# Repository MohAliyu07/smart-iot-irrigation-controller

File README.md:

# Smart IoT Irrigation Controller v2

A four-zone garden watering controller built around the ESP32-S3. It reads four soil-moisture sensors and a DHT11, decides which zones need water, and runs a 12 V pump through four solenoid valves. You can watch it and take over from your phone through Blynk.

This repo has everything for v2: firmware, the PCB, simulations, test results and the technical report.

The current board is **Rev B**, a 100 × 75 mm rectangular board redrawn from the schematic up. The first board (Rev A, the round one) is still here for reference.

## What it does

- Waters each zone on its own. A zone starts below 35 % moisture and stops above 60 % (both adjustable from Blynk).
- Opens at most two valves at once, so the 12 V 3 A adapter is never overloaded.
- Soft-starts the pump over 500 ms with 20 kHz PWM, which cut the start-up peak from 2.98 A to 1.62 A in the performance model.
- Checks the current on every step of the soft start, so a stalled pump is stopped during the ramp (2.54 A after 429 ms in the model).
- Measures pump current with a 20 mΩ shunt and an INA181, and stops the pump within 250 ms on:
  - overcurrent above 2.5 A (jammed pump),
  - dry run below 0.25 A (empty tank),
  - supply voltage outside 10.5–13.8 V.
- Caps every watering run at 20 minutes in case a sensor fails.
- Skips a zone whose soil sensor is shorted, open or unplugged.
- Has three modes (auto, manual and off), a MODE button, a buzzer for faults and a Wi-Fi status LED.

## Hardware

- **MCU:** ESP32-S3-WROOM-1-N8
- **Inputs:** 4 capacitive soil-moisture sensors (power switched by a P-FET to cut corrosion and current), DHT11, supply sense divider (100k/22k), pump current sense
- **Outputs:** 12 V DC pump (PWM low-side MOSFET), 4 × 12 V solenoid valves, buzzer, LEDs
- **Board (Rev B):** 100 × 75 mm rectangle with four M3 mounting holes, routed in EasyEDA Pro with 0 DRC errors and 100 % of nets routed. The DC jack and USB-C face out of the left edge, the pump and valve terminals are along the bottom edge, and the sensor connectors are on the right. The antenna sits at the top edge over a copper keep-out.

### What changed from Rev A to Rev B

- Pump MOSFET changed from AO3400A (SOT-23) to AO4404B (SOIC-8) for more current and heat margin.
- A 1 kΩ + 100 nF filter was added on the current-sense output, because the shunt only carries current during the PWM on-time.
- High-current tracks are 1.4–1.5 mm wide with no vias. Power parts are grouped on the left, away from the antenna and the sensor inputs.
- Unused pins are marked no-connect, and the board has mounting holes.
- Pin assignments are the same, so the pin map in `config.h` did not change.

The schematic is in [hardware/rev-b/schematic/RevB_Schematic.pdf](hardware/rev-b/schematic/RevB_Schematic.pdf). All 7 sheets:

**Sheet 1: Power input**

**Sheet 2: Regulators and USB**

**Sheet 3: ESP32-S3**

**Sheet 4: Soil sensors and DHT11**

**Sheet 5: Pump driver and buzzer**

**Sheet 6: Valves 1 and 2**

**Sheet 7: Valves 3 and 4**

The routed board, with the top copper in red, the bottom copper in blue and the ground pours on both layers:

## Repository layout

| Folder | What's inside |
|---|---|
| `firmware/` | PlatformIO project (Arduino on ESP32-S3) |
| `hardware/rev-b/fab/` | Rev B Gerbers, BOM and pick-and-place from EasyEDA Pro |
| `hardware/rev-b/schematic/` | Rev B schematic, PDF and one PNG per sheet |
| `hardware/rev-a-fab/` | Rev A (round board) Gerbers, BOM and pick-and-place |
| `hardware/kicad/` | Rev A KiCad 10 project |
| `hardware/altium/` | Rev A Altium schematic and PCB |
| `hardware/3d/` | Rev A STEP model |
| `simulation/wokwi/` | Wokwi ESP32-S3 simulation (sketch, diagram, libraries) |
| `simulation/proteus/` | Proteus project, test hex and the automated test runner |
| `simulation/avr-emulator/` | Python AVR emulator used to run the Proteus test firmware and measure timing |
| `simulation/performance-model/` | Plant model in C++ that is compiled with the real firmware sources, plus the CSV output |
| `results/` | Test results workbook and performance graphs |
| `docs/` | Technical report for Rev A (PDF) and the Rev B change notes |
| `images/` | Board and circuit pictures |

## Building the firmware

1. Install [PlatformIO](https://platformio.org/).
2. Copy `firmware/include/secrets.example.h` to `firmware/include/secrets.h` and put in your Wi-Fi name, password and Blynk token. `secrets.h` is git-ignored, so it won't be committed.
3. From `firmware/`, run `pio run -t upload`.

Pin assignments and every limit live in `firmware/include/config.h`.

### Blynk virtual pins

| Pin | Use |
|---|---|
| V0–V3 | Moisture % for zones 1–4 |
| V4, V5 | Temperature, humidity |
| V6 | Supply voltage |
| V7 | Pump current |
| V8 | Mode (0 auto, 1 manual, 2 off) |
| V9 | Fault code |
| V10–V13 | Manual valve switches |
| V14, V15 | Dry and wet thresholds |
| V16 | Clear fault |

## Simulation and testing

- **Wokwi:** open a new ESP32-S3 project and paste in the three files from `simulation/wokwi/`. The pots stand in for the sensors. See that folder's README for the pin map.
- **Proteus:** `simulation/proteus/Irrigation_v2_Sim.pdsprj` runs a stepped test of the pump, valve and alarm outputs.
- **Performance model:** Wokwi only runs at about 3 % of real time, so long runs (an 8-hour watering day, a jammed pump, a dry tank) were done in the C++ model.

```bash
cd simulation/performance-model
F=../../firmware
g++ -O2 -std=c++17 -DREVA -o simA sim.cpp && ./simA
g++ -O2 -std=c++17 -Istub -I$F/include -o sim sim.cpp $F/src/sensors.cpp $F/src/outputs.cpp $F/src/zones.cpp && ./sim
python3 plot.py
```

| Result | Value |
|---|---|
| Most valves open at once | 2 (limit 2) |
| Peak running current | 1.59 A (limit 2.5 A) |
| Soft-start peak | 1.62 A (2.98 A hard start) |
| Dry-run and overcurrent trip time | 250 ms |
| Low-supply trip time | 200–250 ms, tested at 8 points of the 10 s sensor period |
| Faults in a normal 8-hour run | 0 |
| Current-sense error during soft start | 0.01 A mean on Rev B (0.34 A on Rev A) |
| Stalled pump at start-up | stopped at 2.54 A after 429 ms on Rev B (2.94 A, 499 ms on Rev A) |

These numbers come from the model. The Rev B sketch compiles and runs in Wokwi (steady readings, no fault), but the fault tests were not repeated there. The firmware has not been built with PlatformIO or run on a board yet, and Proteus was last run on the Rev A code.

### Proteus check (early logic test)

Before the ESP32 firmware was ready, I tested the watering logic in Proteus on a simplified ATmega328P version. This was done on the Rev A code, not on the Rev B board. Four potentiometers stand in for the soil sensors, a DHT11 gives temperature and humidity, a push button and a switch act as the manual and tank-level inputs, and six LEDs show the pump, the four valves and the alarm. All 6 Proteus tests passed. The project is in `simulation/proteus/`.

The full write-up, including Rev B, is in [docs/Technical_Report_RevB.pdf](docs/Technical_Report_RevB.pdf). The Rev B changes are also listed in [docs/CHANGES_RevB.md](docs/CHANGES_RevB.md).

## Author

Mohammed Olamilekan Aliyu, Electronics Engineer

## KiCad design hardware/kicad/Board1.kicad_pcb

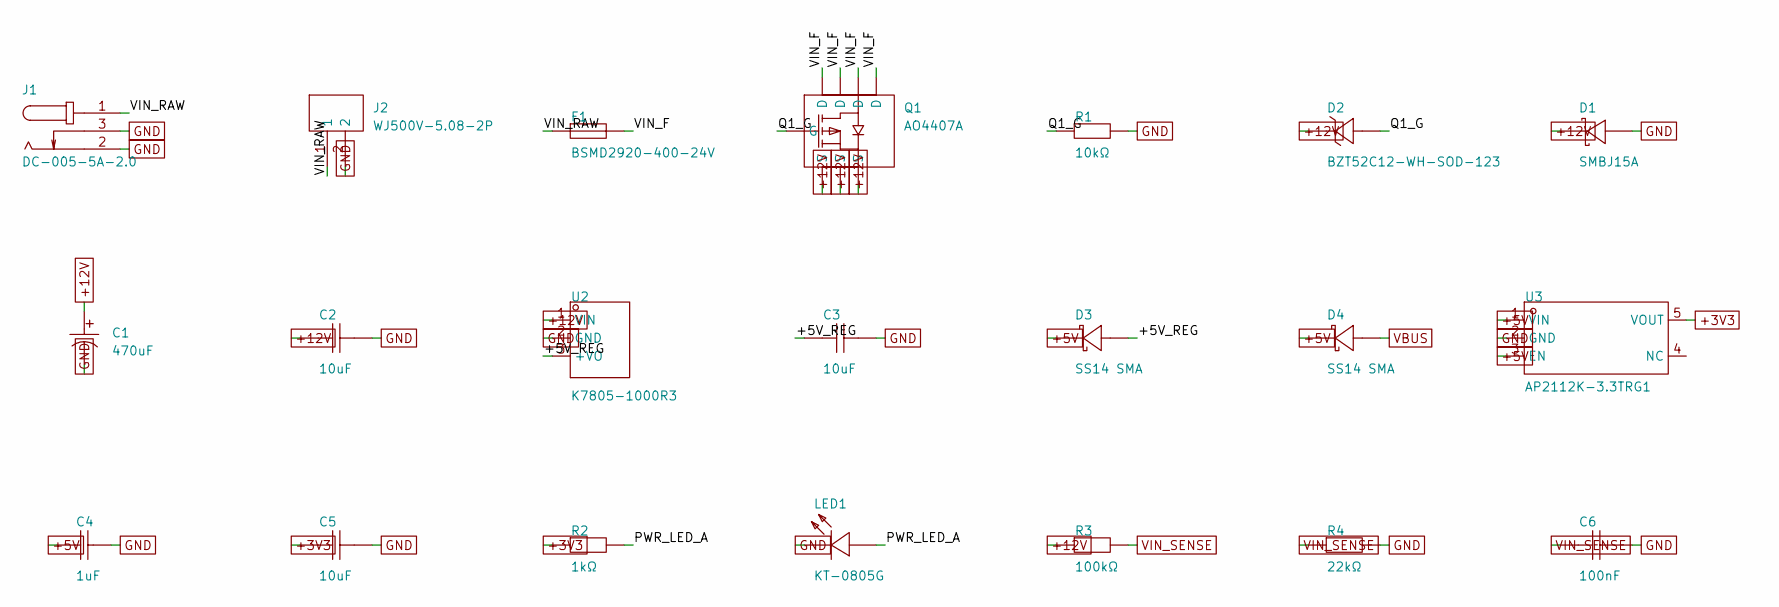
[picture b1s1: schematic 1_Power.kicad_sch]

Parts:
C1: 470uF; CAP-SMD_BD10.0-L10.3-W10.3-LS11.0-FD; TOLERANCE ±20%; VOLTAGE RATING 25V; MANUFACTURER PART RVT1E471M1010; JLCPCB PART CLASS Extended Part
C2, C3, C5: 10uF; C0805; TOLERANCE ±10%; VOLTAGE RATING 25V; MANUFACTURER PART CL21A106KAYNNNE; LCSC PART NAME 10uF ±10% 25V
C4: 1uF; C0805; TOLERANCE ±10%; VOLTAGE RATING 50V; MANUFACTURER PART CL21B105KBFNNNE; JLCPCB PART CLASS Basic Part
C6: 100nF; C0805; TOLERANCE ±10%; VOLTAGE RATING 50V; MANUFACTURER PART CC0805KRX7R9BB104; LCSC PART NAME 100nF ±10% 50V
D1: SMBJ15A; SMB_L4.6-W3.6-LS5.3-RD; BREAKDOWN VOLTAGE 16.7V; MANUFACTURER PART SMBJ15A; LCSC PART NAME SMBJ15A
D2: BZT52C12-WH-SOD-123; SOD-123_L2.7-W1.7-LS3.8-RD; ZENER VOLTAGE(NOM) 12V; ZENER VOLTAGE(RANGE) 11.4V~12.7V; MANUFACTURER PART BZT52C12-WH-SOD-123; LCSC PART NAME 独立式 耐压:12V 电流:0.1uA@9V
D3, D4: SS14 SMA; SMA_L4.3-W2.6-LS5.1-RD; VOLTAGE - FORWARD(VF@IF) 550mV@1A; VOLTAGE - DC REVERSE(VR) 40V; MANUFACTURER PART SS14 SMA; LCSC PART NAME 电压:40V 电流:1A
F1: BSMD2920-400-24V; F2920; VOLTAGE - MAX 24V; MANUFACTURER PART BSMD2920-400-24V; JLCPCB PART CLASS Extended Part
J1: DC-005-5A-2.0; DC-IN-TH_DC-005-5A-2.0; CURRENT RATING 5A; VOLTAGE RATING (MAX) 24V; MANUFACTURER PART DC-005-5A-2.0; LCSC PART NAME DC电源插座 内径:2mm 外径:6.2mm
J2: WJ500V-5.08-2P; CONN-TH_2P-P5.00_WJ500V-5.08-2P; CURRENT RATING 18A; VOLTAGE RATING (MAX) 250V; MANUFACTURER PART WJ500V-5.08-2P; LCSC PART NAME 1x2P 5.08mm 直插 排数:1 每排P数:2
LED1: KT-0805G; LED0805-R-RD; VOLTAGE - FORWARD(VF) 2.6V~3.1V; MANUFACTURER PART KT-0805G; LCSC PART NAME 0805 翠绿 高亮
Q1: AO4407A; SOIC-8_L4.9-W3.9-P1.27-LS6.0-BL; MANUFACTURER PART AO4407A; LCSC PART NAME 1个P沟道 耐压:30V 电流:12A
R1: 10kΩ; R0805; TOLERANCE ±1%; VOLTAGE-SUPPLY(MAX) 150V; MANUFACTURER PART 0805W8F1002T5E; LCSC PART NAME 厚膜电阻 10kΩ ±1%
R2: 1kΩ; R0805; TOLERANCE ±1%; MANUFACTURER PART 0805W8F1001T5E; LCSC PART NAME 1kΩ ±1% 125mW 厚膜电阻
R3: 100kΩ; R0805; TOLERANCE ±1%; MANUFACTURER PART 0805W8F1003T5E (SMT业务专用); LCSC PART NAME 100kΩ ±1%
R4: 22kΩ; R0805; TOLERANCE ±1%; VOLTAGE-SUPPLY(MAX) 150V; MANUFACTURER PART 0805W8F2202T5E; LCSC PART NAME 厚膜电阻 22kΩ ±1%
U2: K7805-1000R3; PWRM-TH_K78XX-2000; VOLTAGE - SUPPLY 8V~36V; OUTPUT VOLTAGE -5V；5V; MANUFACTURER PART K7805-1000R3; LCSC PART NAME DC/DC模块电源，宽电压输入，非隔离稳压单路输出
U3: AP2112K-3.3TRG1; SOT-25-5_L2.9-W1.6-P0.95-LS2.8-BL; VOLTAGE - SUPPLY 6V; OUTPUT VOLTAGE 3.3V; MANUFACTURER PART AP2112K-3.3TRG1; LCSC PART NAME 3.3V 600mA 6V

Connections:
+3V3: C5.1, R2.1, U3.5 (VOUT); also elsewhere on the board
+5V: C4.1, D3.1 (K), D4.1 (K), U3.1 (VIN), U3.3 (EN); also elsewhere on the board
+12V: C1.1, C2.1, D1.1 (K), D2.1 (K), Q1.1 (S), Q1.2 (S), Q1.3 (S), R3.1, U2.1 (VIN); also elsewhere on the board
/1_Power/+5V_REG: C3.1, D3.2 (A), U2.3 (+VO)
/1_Power/PWR_LED_A: LED1.1 (A), R2.2
/1_Power/Q1_G: D2.2 (A), Q1.4 (G), R1.1
/1_Power/VIN_F: F1.2, Q1.5 (D), Q1.6 (D), Q1.7 (D), Q1.8 (D)
/1_Power/VIN_RAW: F1.1, J1.1, J2.1
GND: C1.2, C2.2, C3.2, C4.2, C5.2, C6.2, D1.2 (A), J1.2, J1.3, J2.2, LED1.2 (K), R1.2, R4.2, U2.2 (GND), U3.2 (GND); also elsewhere on the board
VBUS: D4.2 (A); also elsewhere on the board
VIN_SENSE: C6.1, R3.2, R4.1; also elsewhere on the board

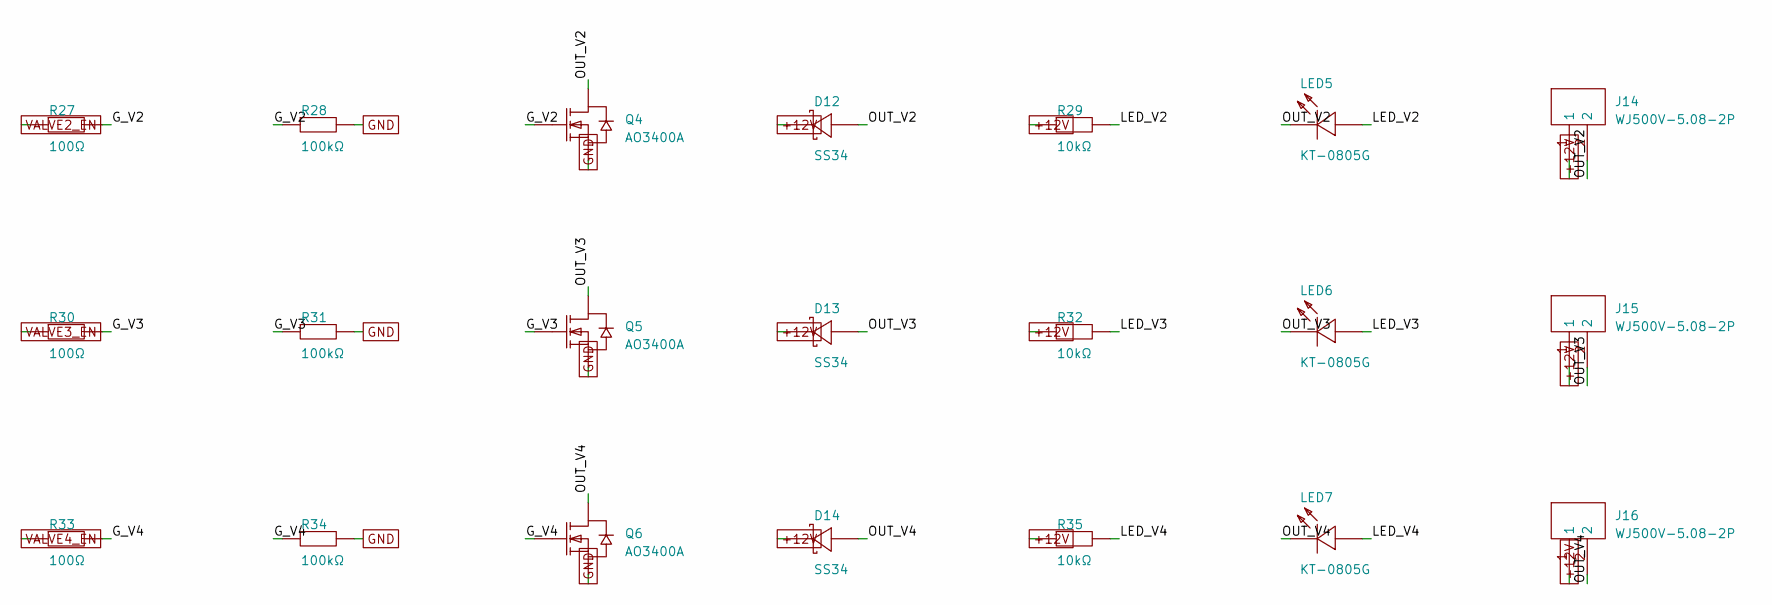
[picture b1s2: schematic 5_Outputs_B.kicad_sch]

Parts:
D12, D13, D14: SS34; SMA_L4.3-W2.6-LS5.2-RD; VOLTAGE - FORWARD(VF@IF) 550mV@3A; VOLTAGE - DC REVERSE(VR) 40V; MANUFACTURER PART SS34; LCSC PART NAME 电压:40V 电流:3A
J14, J15, J16: WJ500V-5.08-2P; CONN-TH_2P-P5.00_WJ500V-5.08-2P; CURRENT RATING 18A; VOLTAGE RATING (MAX) 250V; MANUFACTURER PART WJ500V-5.08-2P; LCSC PART NAME 1x2P 5.08mm 直插 排数:1 每排P数:2
LED5, LED6, LED7: KT-0805G; LED0805-R-RD; VOLTAGE - FORWARD(VF) 2.6V~3.1V; MANUFACTURER PART KT-0805G; LCSC PART NAME 0805 翠绿 高亮
Q4, Q5, Q6: AO3400A; SOT-23-3_L2.9-W1.3-P1.90-LS2.4-BR; MANUFACTURER PART AO3400A; LCSC PART NAME N沟道 耐压:30V
R27, R30, R33: 100Ω; R0805; TOLERANCE ±1%; MANUFACTURER PART 0805W8F1000T5E; LCSC PART NAME 100Ω ±1% 125mW 厚膜电阻
R28, R31, R34: 100kΩ; R0805; TOLERANCE ±1%; MANUFACTURER PART 0805W8F1003T5E (SMT业务专用); LCSC PART NAME 100kΩ ±1%
R29, R32, R35: 10kΩ; R0805; TOLERANCE ±1%; VOLTAGE-SUPPLY(MAX) 150V; MANUFACTURER PART 0805W8F1002T5E; LCSC PART NAME 厚膜电阻 10kΩ ±1%

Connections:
+12V: D12.1 (K), D13.1 (K), D14.1 (K), J14.1, J15.1, J16.1, R29.1, R32.1, R35.1; also elsewhere on the board
/5_Outputs_B/G_V2: Q4.1 (G), R27.2, R28.1
/5_Outputs_B/G_V3: Q5.1 (G), R30.2, R31.1
/5_Outputs_B/G_V4: Q6.1 (G), R33.2, R34.1
/5_Outputs_B/LED_V2: LED5.1 (A), R29.2
/5_Outputs_B/LED_V3: LED6.1 (A), R32.2
/5_Outputs_B/LED_V4: LED7.1 (A), R35.2
/5_Outputs_B/OUT_V2: D12.2 (A), J14.2, LED5.2 (K), Q4.3 (D)
/5_Outputs_B/OUT_V3: D13.2 (A), J15.2, LED6.2 (K), Q5.3 (D)
/5_Outputs_B/OUT_V4: D14.2 (A), J16.2, LED7.2 (K), Q6.3 (D)
GND: Q4.2 (S), Q5.2 (S), Q6.2 (S), R28.2, R31.2, R34.2; also elsewhere on the board
VALVE2_EN: R27.1; also elsewhere on the board
VALVE3_EN: R30.1; also elsewhere on the board
VALVE4_EN: R33.1; also elsewhere on the board

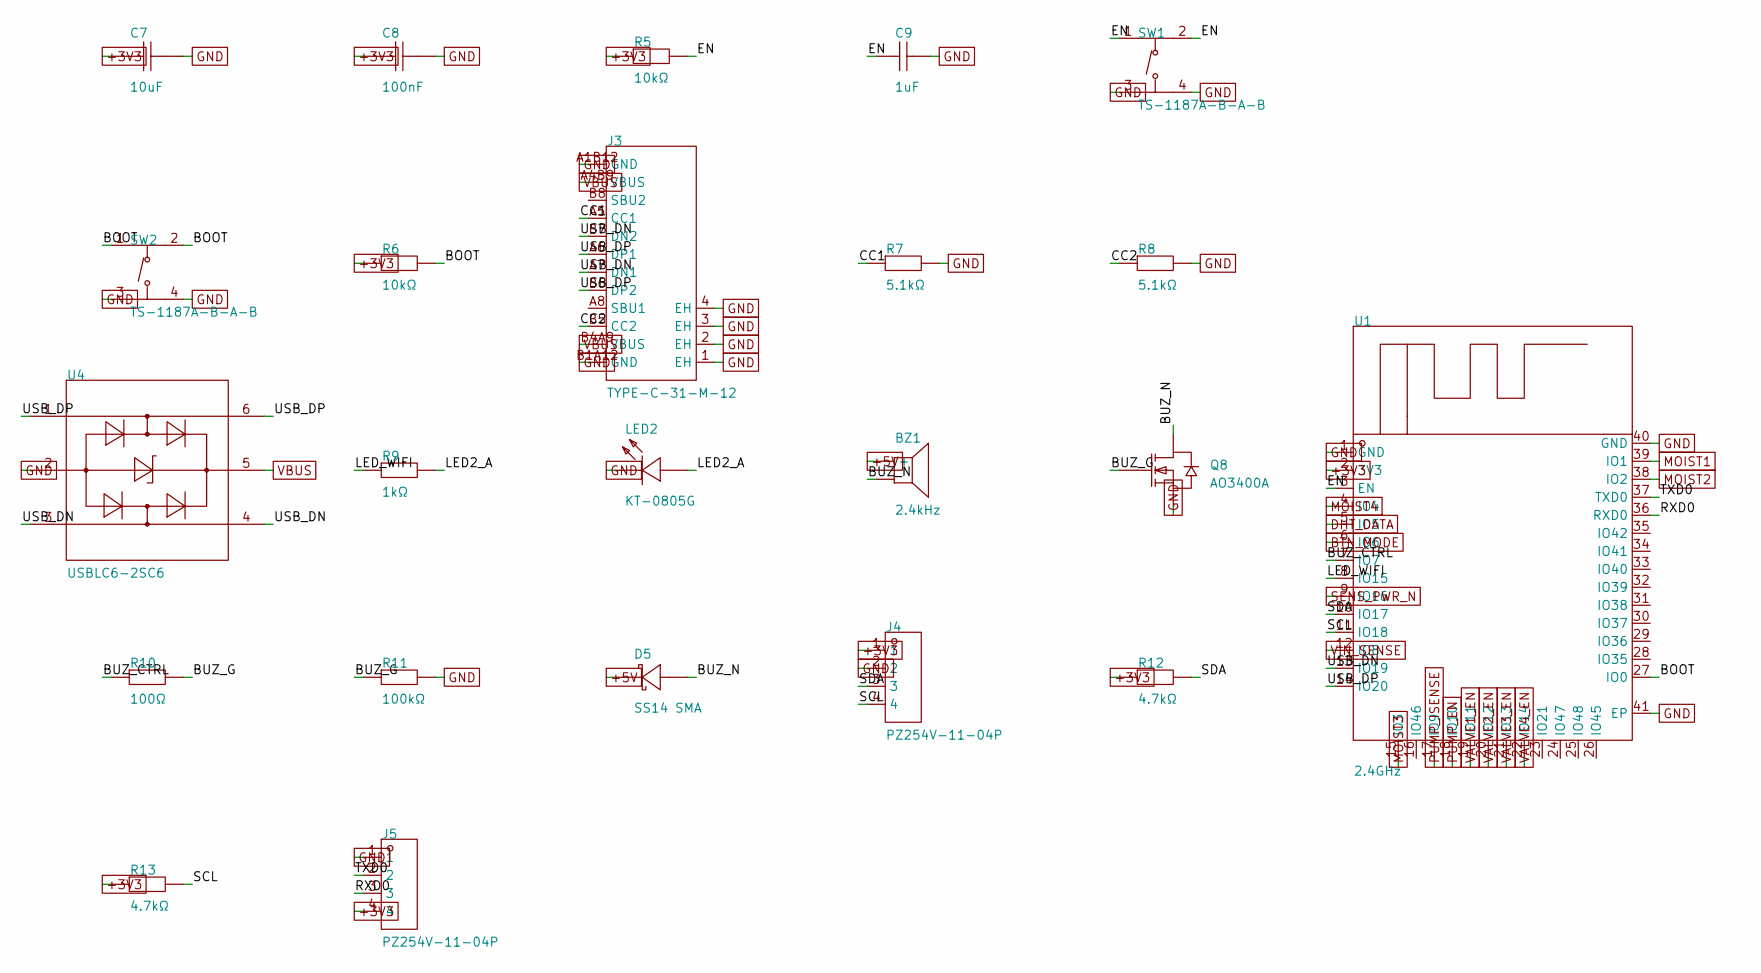
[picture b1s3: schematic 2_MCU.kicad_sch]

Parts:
BZ1: 2.4kHz; BUZ-TH_BD12.0-P7.60-D0.6-FD; VOLTAGE RATING 5V; VOLTAGE - SUPPLY 4V~8V; MANUFACTURER PART TMB12A05; LCSC PART NAME 有源(内含驱动线路) 电磁式 2.4kHz
C7: 10uF; C0805; TOLERANCE ±10%; VOLTAGE RATING 25V; MANUFACTURER PART CL21A106KAYNNNE; LCSC PART NAME 10uF ±10% 25V
C8: 100nF; C0805; TOLERANCE ±10%; VOLTAGE RATING 50V; MANUFACTURER PART CC0805KRX7R9BB104; LCSC PART NAME 100nF ±10% 50V
C9: 1uF; C0805; TOLERANCE ±10%; VOLTAGE RATING 50V; MANUFACTURER PART CL21B105KBFNNNE; JLCPCB PART CLASS Basic Part
D5: SS14 SMA; SMA_L4.3-W2.6-LS5.1-RD; VOLTAGE - FORWARD(VF@IF) 550mV@1A; VOLTAGE - DC REVERSE(VR) 40V; MANUFACTURER PART SS14 SMA; LCSC PART NAME 电压:40V 电流:1A
J3: TYPE-C-31-M-12; USB-C_SMD-TYPE-C-31-M-12_1; CURRENT RATING-POWER 5A; VOLTAGE RATING 20V; MANUFACTURER PART TYPE-C-31-M-12; LCSC PART NAME Type-C 母 卧贴
J4, J5: PZ254V-11-04P; HDR-TH_4P-P2.54-V-M; CURRENT RATING 3A; VOLTAGE RATING (MAX) 250V; MANUFACTURER PART PZ254V-11-04P; LCSC PART NAME 1x4P 间距:2.54mm 方针 直插
LED2: KT-0805G; LED0805-R-RD; VOLTAGE - FORWARD(VF) 2.6V~3.1V; MANUFACTURER PART KT-0805G; LCSC PART NAME 0805 翠绿 高亮
Q8: AO3400A; SOT-23-3_L2.9-W1.3-P1.90-LS2.4-BR; MANUFACTURER PART AO3400A; LCSC PART NAME N沟道 耐压:30V
R5, R6: 10kΩ; R0805; TOLERANCE ±1%; VOLTAGE-SUPPLY(MAX) 150V; MANUFACTURER PART 0805W8F1002T5E; LCSC PART NAME 厚膜电阻 10kΩ ±1%
R7, R8: 5.1kΩ; R0805; TOLERANCE ±1%; VOLTAGE-SUPPLY(MAX) 150V; MANUFACTURER PART 0805W8F5101T5E; LCSC PART NAME 厚膜电阻 5.1kΩ ±1%
R9: 1kΩ; R0805; TOLERANCE ±1%; MANUFACTURER PART 0805W8F1001T5E; LCSC PART NAME 1kΩ ±1% 125mW 厚膜电阻
R10: 100Ω; R0805; TOLERANCE ±1%; MANUFACTURER PART 0805W8F1000T5E; LCSC PART NAME 100Ω ±1% 125mW 厚膜电阻
R11: 100kΩ; R0805; TOLERANCE ±1%; MANUFACTURER PART 0805W8F1003T5E (SMT业务专用); LCSC PART NAME 100kΩ ±1%
R12, R13: 4.7kΩ; R0805; TOLERANCE ±1%; MANUFACTURER PART 0805W8F4701T5E; LCSC PART NAME 4.7kΩ ±1% 125mW 厚膜电阻
SW1, SW2: TS-1187A-B-A-B; SW-SMD_4P-L5.1-W5.1-P3.70-LS6.5-TL_H1.5; VOLTAGE RATING 12V; MANUFACTURER PART TS-1187A-B-A-B; LCSC PART NAME 5.1*5.1*1.5mm 立贴 轻触开关
U1: 2.4GHz; WIFIM-SMD_ESP32-S3-WROOM-1-N8; VOLTAGE - SUPPLY 3V~3.6V; MANUFACTURER PART ESP32-S3-WROOM-1-N8; LCSC PART NAME 不带固件 不带固件 通用型Wi-Fi+低功耗蓝牙MCU模组
U4: USBLC6-2SC6; SOT-23-6_L2.9-W1.6-P0.95-LS2.8-BL; CLAMPING VOLTAGE 17V; VOLTAGE - BREAKDOWN 6V; MANUFACTURER PART USBLC6-2SC6; LCSC PART NAME 单向ESD 5.25V截止 峰值脉冲电流：5A

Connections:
+3V3: C7.1, C8.1, J4.1, J5.4, R5.1, R6.1, R12.1, R13.1, U1.2 (3V3); also elsewhere on the board
+5V: BZ1.1 (+), D5.1 (K); also elsewhere on the board
/2_MCU/BOOT: R6.2, SW2.1 (A), SW2.2 (B), U1.27 (IO0)
/2_MCU/BUZ_CTRL: R10.1, U1.7 (IO7)
/2_MCU/BUZ_G: Q8.1 (G), R10.2, R11.1
/2_MCU/BUZ_N: BZ1.2, D5.2 (A), Q8.3 (D)
/2_MCU/CC1: J3.A5 (CC1), R7.1
/2_MCU/CC2: J3.B5 (CC2), R8.1
/2_MCU/EN: C9.1, R5.2, SW1.1 (A), SW1.2 (B), U1.3 (EN)
/2_MCU/LED2_A: LED2.1 (A), R9.2
/2_MCU/LED_WIFI: R9.1, U1.8 (IO15)
/2_MCU/RXD0: J5.3, U1.36 (RXD0)
/2_MCU/SCL: J4.4, R13.2, U1.11 (IO18)
/2_MCU/SDA: J4.3, R12.2, U1.10 (IO17)
/2_MCU/TXD0: J5.2, U1.37 (TXD0)
/2_MCU/USB_DN: J3.A7 (DN1), J3.B7 (DN2), U1.13 (IO19), U4.3, U4.4
/2_MCU/USB_DP: J3.A6 (DP1), J3.B6 (DP2), U1.14 (IO20), U4.1, U4.6
BTN_MODE: U1.6 (IO6); also elsewhere on the board
DHT_DATA: U1.5 (IO5); also elsewhere on the board
GND: C7.2, C8.2, C9.2, J3.1 (EH), J3.2 (EH), J3.3 (EH), J3.4 (EH), J3.A1B12 (GND), J3.B1A12 (GND), J4.2, J5.1, LED2.2 (K), Q8.2 (S), R7.2, R8.2, R11.2, SW1.3 (C), SW1.4 (D), SW2.3 (C), SW2.4 (D), U1.1 (GND), U1.40 (GND), U1.41 (EP), U4.2; also elsewhere on the board
MOIST1: U1.39 (IO1); also elsewhere on the board
MOIST2: U1.38 (IO2); also elsewhere on the board
MOIST3: U1.15 (IO3); also elsewhere on the board
MOIST4: U1.4 (IO4); also elsewhere on the board
PUMP_EN: U1.18 (IO10); also elsewhere on the board
PUMP_ISENSE: U1.17 (IO9); also elsewhere on the board
SENS_PWR_N: U1.9 (IO16); also elsewhere on the board
VALVE1_EN: U1.19 (IO11); also elsewhere on the board
VALVE2_EN: U1.20 (IO12); also elsewhere on the board
VALVE3_EN: U1.21 (IO13); also elsewhere on the board
VALVE4_EN: U1.22 (IO14); also elsewhere on the board
VBUS: J3.A4B9 (VBUS), J3.B4A9 (VBUS), U4.5; also elsewhere on the board
VIN_SENSE: U1.12 (IO8); also elsewhere on the board

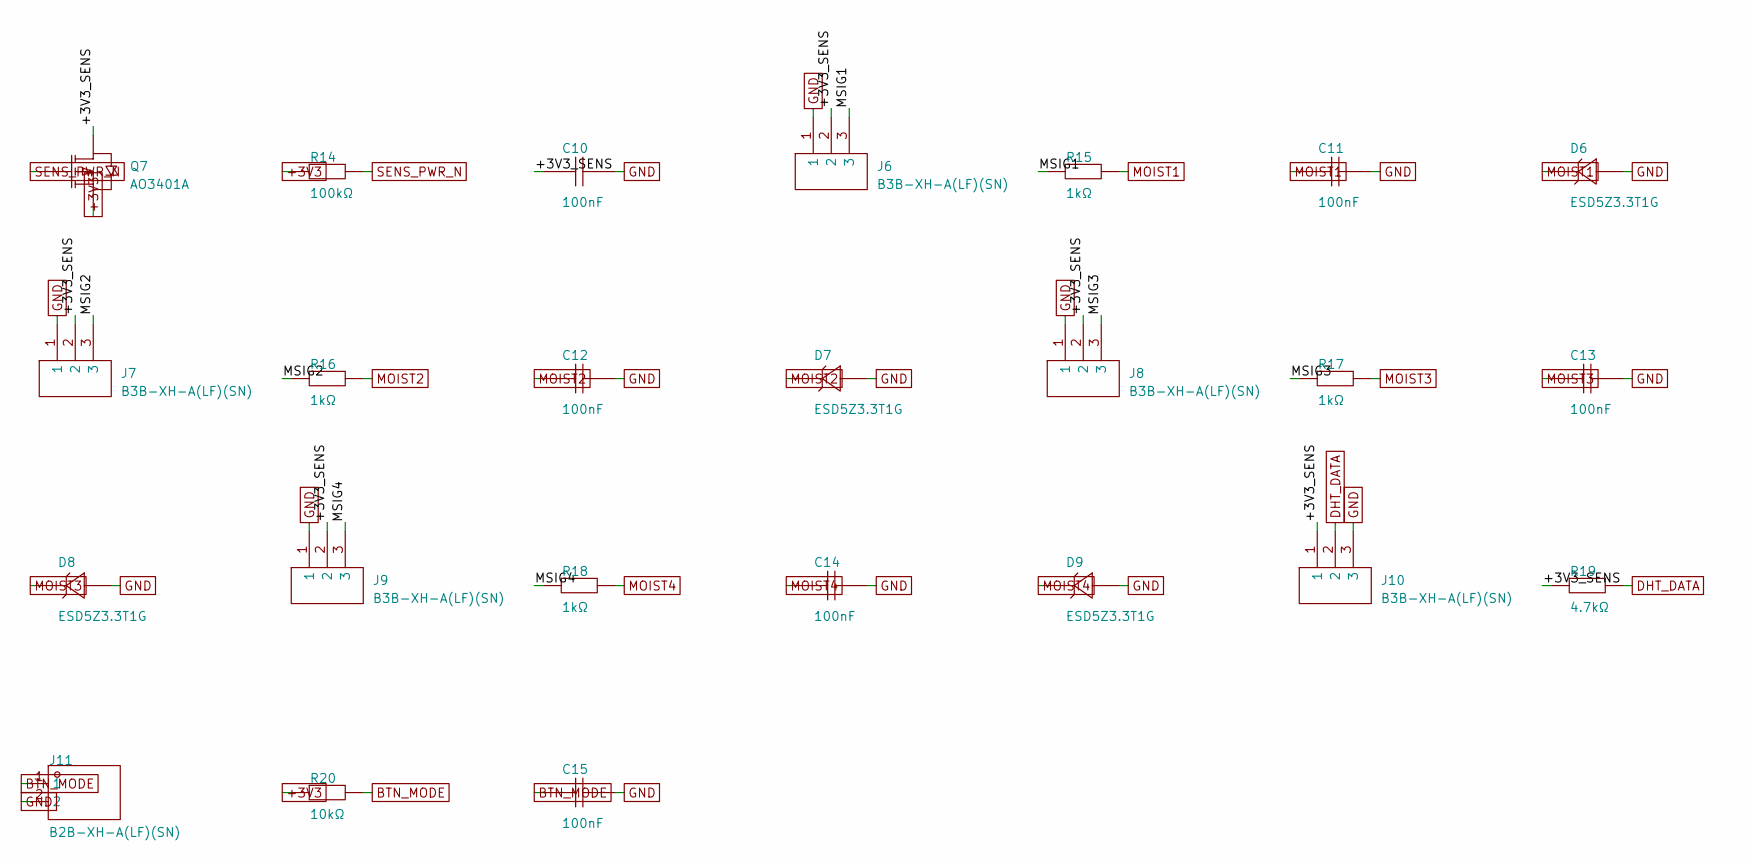
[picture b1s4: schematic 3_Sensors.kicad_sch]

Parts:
C10, C11, C12, C13, C14, C15: 100nF; C0805; TOLERANCE ±10%; VOLTAGE RATING 50V; MANUFACTURER PART CC0805KRX7R9BB104; LCSC PART NAME 100nF ±10% 50V
D6, D7, D8, D9: ESD5Z3.3T1G; SOD-523_L1.2-W0.8-LS1.6-FD; CLAMPING VOLTAGE 14V; VOLTAGE - BREAKDOWN 5V; MANUFACTURER PART ESD5Z3.3T1G; LCSC PART NAME 单向ESD 3.3V截止 峰值浪涌电流：11A
J6, J7, J8, J9, J10: B3B-XH-A(LF)(SN); CONN-TH_3P-P2.50_A2501WV2-3P; CURRENT RATING 3A; VOLTAGE RATING 250V; MANUFACTURER PART B3B-XH-A(LF)(SN); LCSC PART NAME 1x3P 间距:2.5mm 直插 系列:XH
J11: B2B-XH-A(LF)(SN); CONN-TH_B2B-XH-A-LF-SN; CURRENT RATING 3A; VOLTAGE RATING 250V; MANUFACTURER PART B2B-XH-A(LF)(SN); LCSC PART NAME 1x2P 间距:2.5mm 直插 系列:XH
Q7: AO3401A; SOT-23_L2.9-W1.3-P1.90-LS2.4-BR; MANUFACTURER PART AO3401A; LCSC PART NAME 1个P沟道 耐压:30V 电流:4A
R14: 100kΩ; R0805; TOLERANCE ±1%; MANUFACTURER PART 0805W8F1003T5E (SMT业务专用); LCSC PART NAME 100kΩ ±1%
R15, R16, R17, R18: 1kΩ; R0805; TOLERANCE ±1%; MANUFACTURER PART 0805W8F1001T5E; LCSC PART NAME 1kΩ ±1% 125mW 厚膜电阻
R19: 4.7kΩ; R0805; TOLERANCE ±1%; MANUFACTURER PART 0805W8F4701T5E; LCSC PART NAME 4.7kΩ ±1% 125mW 厚膜电阻
R20: 10kΩ; R0805; TOLERANCE ±1%; VOLTAGE-SUPPLY(MAX) 150V; MANUFACTURER PART 0805W8F1002T5E; LCSC PART NAME 厚膜电阻 10kΩ ±1%

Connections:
+3V3: Q7.2 (S), R14.1, R20.1; also elsewhere on the board
/3_Sensors/+3V3_SENS: C10.1, J6.2, J7.2, J8.2, J9.2, J10.1, Q7.3 (D), R19.1
/3_Sensors/MSIG1: J6.3, R15.1
/3_Sensors/MSIG2: J7.3, R16.1
/3_Sensors/MSIG3: J8.3, R17.1
/3_Sensors/MSIG4: J9.3, R18.1
BTN_MODE: C15.1, J11.1, R20.2; also elsewhere on the board
DHT_DATA: J10.2, R19.2; also elsewhere on the board
GND: C10.2, C11.2, C12.2, C13.2, C14.2, C15.2, D6.1 (A), D7.1 (A), D8.1 (A), D9.1 (A), J6.1, J7.1, J8.1, J9.1, J10.3, J11.2; also elsewhere on the board
MOIST1: C11.1, D6.2 (K), R15.2; also elsewhere on the board
MOIST2: C12.1, D7.2 (K), R16.2; also elsewhere on the board
MOIST3: C13.1, D8.2 (K), R17.2; also elsewhere on the board
MOIST4: C14.1, D9.2 (K), R18.2; also elsewhere on the board
SENS_PWR_N: Q7.1 (G), R14.2; also elsewhere on the board

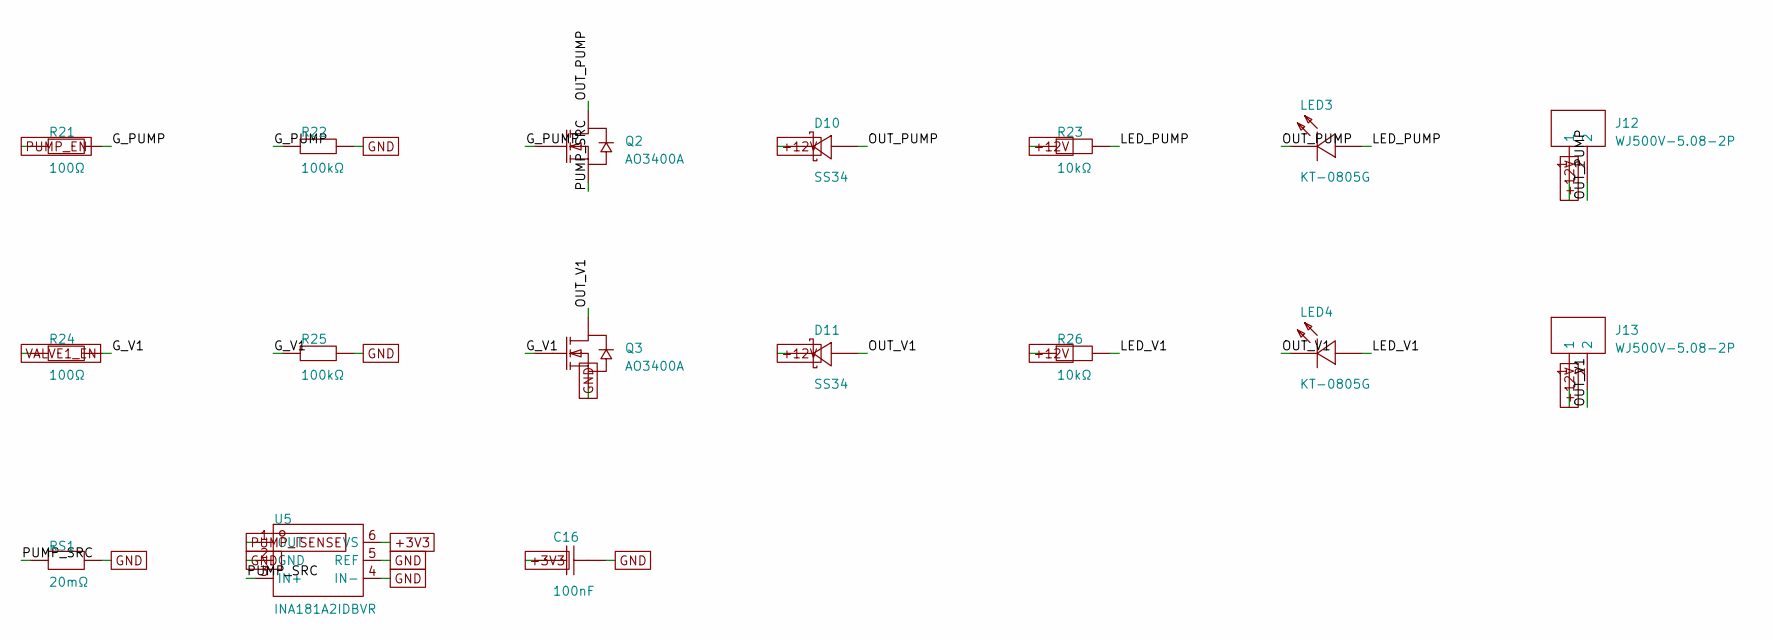
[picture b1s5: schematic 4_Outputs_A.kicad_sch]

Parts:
C16: 100nF; C0805; TOLERANCE ±10%; VOLTAGE RATING 50V; MANUFACTURER PART CC0805KRX7R9BB104; LCSC PART NAME 100nF ±10% 50V
D10, D11: SS34; SMA_L4.3-W2.6-LS5.2-RD; VOLTAGE - FORWARD(VF@IF) 550mV@3A; VOLTAGE - DC REVERSE(VR) 40V; MANUFACTURER PART SS34; LCSC PART NAME 电压:40V 电流:3A
J12, J13: WJ500V-5.08-2P; CONN-TH_2P-P5.00_WJ500V-5.08-2P; CURRENT RATING 18A; VOLTAGE RATING (MAX) 250V; MANUFACTURER PART WJ500V-5.08-2P; LCSC PART NAME 1x2P 5.08mm 直插 排数:1 每排P数:2
LED3, LED4: KT-0805G; LED0805-R-RD; VOLTAGE - FORWARD(VF) 2.6V~3.1V; MANUFACTURER PART KT-0805G; LCSC PART NAME 0805 翠绿 高亮
Q2, Q3: AO3400A; SOT-23-3_L2.9-W1.3-P1.90-LS2.4-BR; MANUFACTURER PART AO3400A; LCSC PART NAME N沟道 耐压:30V
R21, R24: 100Ω; R0805; TOLERANCE ±1%; MANUFACTURER PART 0805W8F1000T5E; LCSC PART NAME 100Ω ±1% 125mW 厚膜电阻
R22, R25: 100kΩ; R0805; TOLERANCE ±1%; MANUFACTURER PART 0805W8F1003T5E (SMT业务专用); LCSC PART NAME 100kΩ ±1%
R23, R26: 10kΩ; R0805; TOLERANCE ±1%; VOLTAGE-SUPPLY(MAX) 150V; MANUFACTURER PART 0805W8F1002T5E; LCSC PART NAME 厚膜电阻 10kΩ ±1%
RS1: 20mΩ; R2512; TOLERANCE ±1%; MANUFACTURER PART HoJLR2512-2W-20mR-1%-75ppm; JLCPCB PART CLASS Extended Part
U5: INA181A2IDBVR; SOT-23-6_L2.9-W1.6-P0.95-LS2.8-BL; DIFFERENTIAL VOLTAGE ±26V; MANUFACTURER PART INA181A2IDBVR; LCSC PART NAME 双向低侧和高侧电压输出电流感应放大器

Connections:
+3V3: C16.1, U5.6 (VS); also elsewhere on the board
+12V: D10.1 (K), D11.1 (K), J12.1, J13.1, R23.1, R26.1; also elsewhere on the board
/4_Outputs_A/G_PUMP: Q2.1 (G), R21.2, R22.1
/4_Outputs_A/G_V1: Q3.1 (G), R24.2, R25.1
/4_Outputs_A/LED_PUMP: LED3.1 (A), R23.2
/4_Outputs_A/LED_V1: LED4.1 (A), R26.2
/4_Outputs_A/OUT_PUMP: D10.2 (A), J12.2, LED3.2 (K), Q2.3 (D)
/4_Outputs_A/OUT_V1: D11.2 (A), J13.2, LED4.2 (K), Q3.3 (D)
/4_Outputs_A/PUMP_SRC: Q2.2 (S), RS1.1, U5.3 (IN+)
GND: C16.2, Q3.2 (S), R22.2, R25.2, RS1.2, U5.2 (GND), U5.4 (IN-), U5.5 (REF); also elsewhere on the board
PUMP_EN: R21.1; also elsewhere on the board
PUMP_ISENSE: U5.1 (OUT); also elsewhere on the board
VALVE1_EN: R24.1; also elsewhere on the board

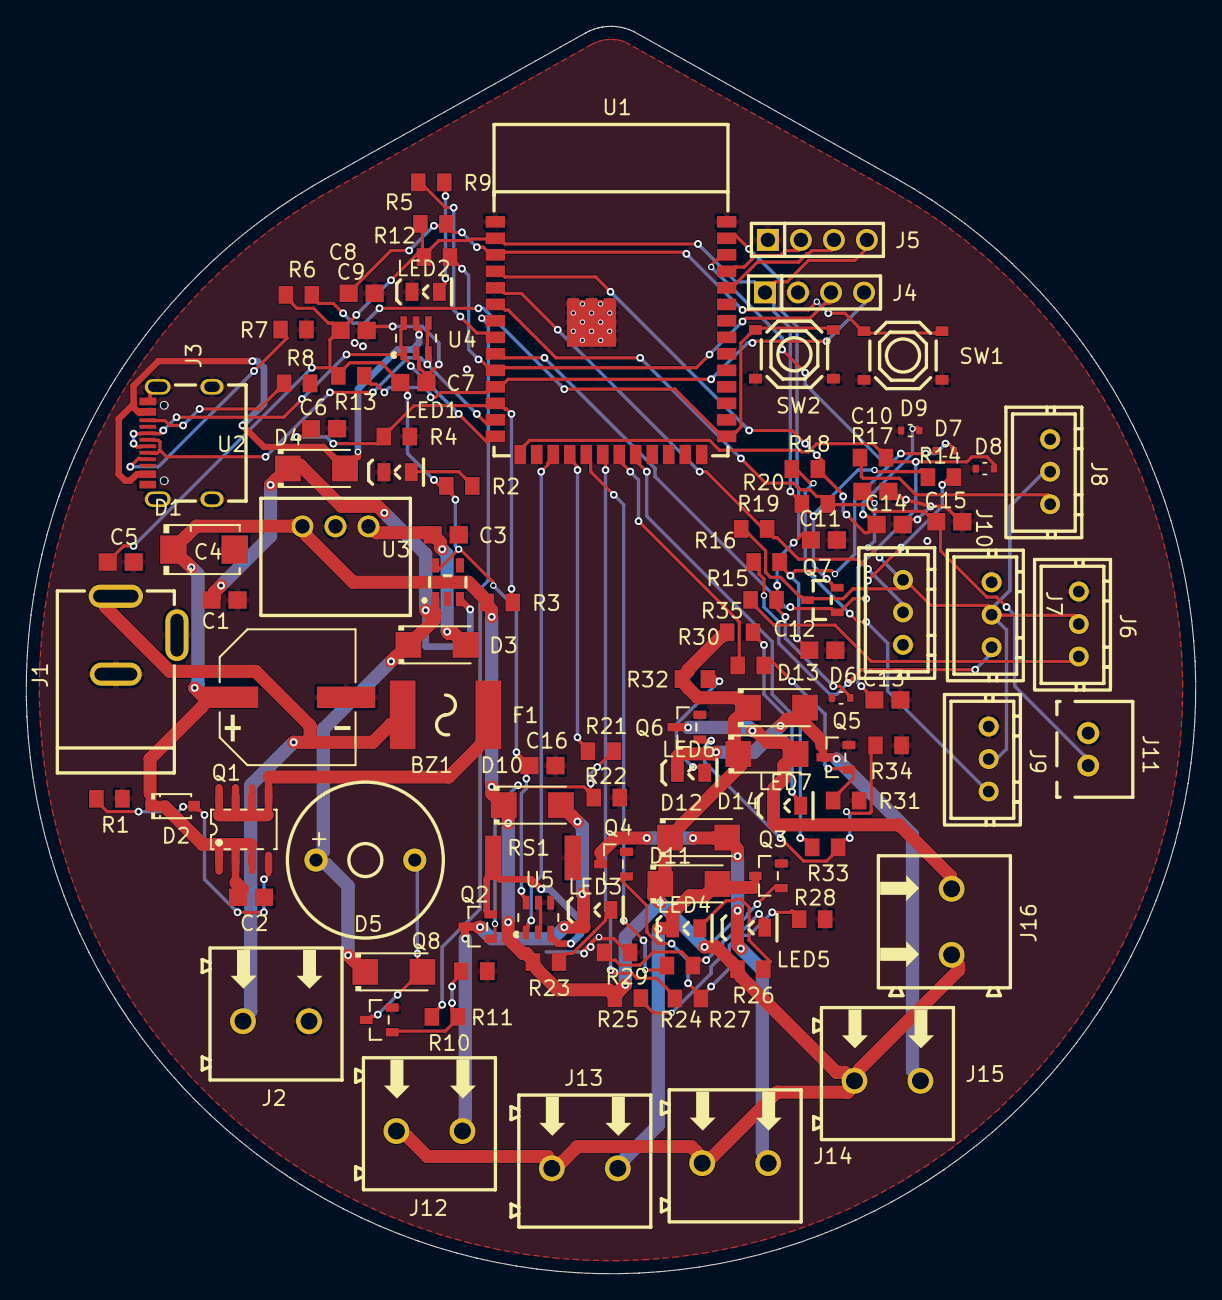
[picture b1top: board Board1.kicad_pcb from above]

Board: 2 copper layers, 90.0 x 96.0 mm, 106 parts (0 on the bottom side), 60 nets.

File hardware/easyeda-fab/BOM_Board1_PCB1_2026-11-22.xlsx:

No. | Quantity | Comment | Designator | Footprint | Value | Manufacturer Part | Manufacturer | Supplier Part | Supplier
1 | 1 | 2.4kHz | BZ1 | BUZ-TH_BD12.0-P7.60-D0.6-FD | 2.4kHz | TMB12A05 | 华能 | C96093 | LCSC
2 | 1 | 470uF | C1 | CAP-SMD_BD10.0-L10.3-W10.3-LS11.0-FD | 470uF | RVT1E471M1010 | HONOR(荣誉) | C3351 | LCSC
3 | 4 | 10uF | C2,C3,C5,C7 | C0805 | 10uF | CL21A106KAYNNNE | SAMSUNG(三星) | C15850 | LCSC
4 | 2 | 1uF | C4,C9 | C0805 | 1uF | CL21B105KBFNNNE | SAMSUNG(三星) | C28323 | LCSC
5 | 9 | 100nF | C6,C8,C10,C11,C12,C13,C14,C15,C16 | C0805 | 100nF | CC0805KRX7R9BB104 | YAGEO(国巨) | C49678 | LCSC
6 | 1 | SMBJ15A | D1 | SMB_L4.6-W3.6-LS5.3-RD |  | SMBJ15A |  | C232769 | LCSC
7 | 1 | BZT52C12-WH-SOD-123 | D2 | SOD-123_L2.7-W1.7-LS3.8-RD |  | BZT52C12-WH-SOD-123 | SY(顺烨) | C5464725 | LCSC
8 | 3 | SS14 SMA | D3,D4,D5 | SMA_L4.3-W2.6-LS5.1-RD |  | SS14 SMA | Yint(音特电子) | C2920036 | LCSC
9 | 4 | ESD5Z3.3T1G | D6,D7,D8,D9 | SOD-523_L1.2-W0.8-LS1.6-FD |  | ESD5Z3.3T1G | TECH PUBLIC(台舟) | C2827729 | LCSC
10 | 5 | SS34 | D10,D11,D12,D13,D14 | SMA_L4.3-W2.6-LS5.2-RD |  | SS34 | MDD(辰达半导体) | C8678 | LCSC
11 | 1 | BSMD2920-400-24V | F1 | F2920 |  | BSMD2920-400-24V | BHFUSE(佰宏) | C960036 | LCSC
12 | 1 | DC-005-5A-2.0 | J1 | DC-IN-TH_DC-005-5A-2.0 |  | DC-005-5A-2.0 | XKB Connection(中国星坤) | C381116 | LCSC
13 | 6 | WJ500V-5.08-2P | J2,J12,J13,J14,J15,J16 | CONN-TH_2P-P5.00_WJ500V-5.08-2P |  | WJ500V-5.08-2P | KANGNEX(康奈克斯电气) | C8465 | LCSC
14 | 1 | TYPE-C-31-M-12 | J3 | USB-C_SMD-TYPE-C-31-M-12_1 |  | TYPE-C-31-M-12 | 韩国韩荣 | C165948 | LCSC
15 | 2 | PZ254V-11-04P | J4,J5 | HDR-TH_4P-P2.54-V-M |  | PZ254V-11-04P | XFCN(兴飞) | C492403 | LCSC
16 | 5 | B3B-XH-A(LF)(SN) | J6,J7,J8,J9,J10 | CONN-TH_3P-P2.50_A2501WV2-3P |  | B3B-XH-A(LF)(SN) | JST | C144394 | LCSC
17 | 1 | B2B-XH-A(LF)(SN) | J11 | CONN-TH_B2B-XH-A-LF-SN |  | B2B-XH-A(LF)(SN) | JST | C158012 | LCSC
18 | 7 | KT-0805G | LED1,LED2,LED3,LED4,LED5,LED6,LED7 | LED0805-R-RD |  | KT-0805G | KENTO | C2297 | LCSC
19 | 1 | AO4407A | Q1 | SOIC-8_L4.9-W3.9-P1.27-LS6.0-BL |  | AO4407A | AOS | C16072 | LCSC
20 | 6 | AO3400A | Q2,Q3,Q4,Q5,Q6,Q8 | SOT-23-3_L2.9-W1.3-P1.90-LS2.4-BR |  | AO3400A | AOS | C20917 | LCSC
21 | 1 | AO3401A | Q7 | SOT-23_L2.9-W1.3-P1.90-LS2.4-BR |  | AO3401A | AOS | C15127 | LCSC
22 | 9 | 10kΩ | R1,R5,R6,R20,R23,R26,R29,R32,R35 | R0805 | 10kΩ | 0805W8F1002T5E | UNI-ROYAL(厚声) | C17414 | LCSC
23 | 6 | 1kΩ | R2,R9,R15,R16,R17,R18 | R0805 | 1kΩ | 0805W8F1001T5E | UNI-ROYAL(厚声) | C17513 | LCSC
24 | 8 | 100kΩ | R3,R11,R14,R22,R25,R28,R31,R34 | R0805 | 100kΩ | 0805W8F1003T5E (SMT业务专用) | UNI-ROYAL(厚声) | C17407 | LCSC
25 | 1 | 22kΩ | R4 | R0805 | 22kΩ | 0805W8F2202T5E | UNI-ROYAL(厚声) | C17560 | LCSC
26 | 2 | 5.1kΩ | R7,R8 | R0805 | 5.1kΩ | 0805W8F5101T5E | UNI-ROYAL(厚声) | C27834 | LCSC
27 | 6 | 100Ω | R10,R21,R24,R27,R30,R33 | R0805 | 100Ω | 0805W8F1000T5E | UNI-ROYAL(厚声) | C17408 | LCSC
28 | 3 | 4.7kΩ | R12,R13,R19 | R0805 | 4.7kΩ | 0805W8F4701T5E | UNI-ROYAL(厚声) | C17673 | LCSC
29 | 1 | 20mΩ | RS1 | R2512 | 20mΩ | HoJLR2512-2W-20mR-1%-75ppm | Milliohm(毫欧) | C2924538 | LCSC
30 | 2 | TS-1187A-B-A-B | SW1,SW2 | SW-SMD_4P-L5.1-W5.1-P3.70-LS6.5-TL_H1.5 |  | TS-1187A-B-A-B | XKB Connection(中国星坤) | C318884 | LCSC
31 | 1 | 2.4GHz | U1 | WIFIM-SMD_ESP32-S3-WROOM-1-N8 | 2.4GHz | ESP32-S3-WROOM-1-N8 | ESPRESSIF(乐鑫) | C2913198 | LCSC
32 | 1 | K7805-1000R3 | U2 | PWRM-TH_K78XX-2000 |  | K7805-1000R3 | MORNSUN(金升阳) | C111280 | LCSC
33 | 1 | AP2112K-3.3TRG1 | U3 | SOT-25-5_L2.9-W1.6-P0.95-LS2.8-BL |  | AP2112K-3.3TRG1 | DIODES(美台) | C51118 | LCSC
34 | 1 | USBLC6-2SC6 | U4 | SOT-23-6_L2.9-W1.6-P0.95-LS2.8-BL |  | USBLC6-2SC6 | ST(意法半导体) | C7519 | LCSC
35 | 1 | INA181A2IDBVR | U5 | SOT-23-6_L2.9-W1.6-P0.95-LS2.8-BL |  | INA181A2IDBVR | TI(德州仪器) | C2058784 | LCSC

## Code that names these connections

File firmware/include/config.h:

// =============================================================================
//  Smart IoT Irrigation Controller v2 - board Rev B
//  config.h : pin map, electrical scaling, limits and defaults
//
//  MCU   : ESP32-S3-WROOM-1-N8
//  Board : Rev B (pump MOSFET AO4404B, INA181A2 output filtered by 1 k + 100 nF)
//  Every number that depends on the hardware lives in this file.
// =============================================================================
#pragma once

// ---- Pin map (matches the Rev B schematic, sheet 3_MCU) ---------------------
#define PIN_MOIST1      1     // ADC1: soil moisture, zone 1
#define PIN_MOIST2      2     // ADC1: soil moisture, zone 2
#define PIN_MOIST3      3     // ADC1: soil moisture, zone 3
#define PIN_MOIST4      4     // ADC1: soil moisture, zone 4
#define PIN_DHT         5     // DHT11 data
#define PIN_BTN_MODE    6     // MODE button, active low
#define PIN_BUZZER      7     // buzzer driver, active high
#define PIN_VIN_SENSE   8     // ADC1: 12 V rail through a 100 k / 22 k divider
#define PIN_PUMP_ISENSE 9     // ADC1: pump current, 1 V per amp
#define PIN_PUMP_EN     10    // pump MOSFET gate, 20 kHz PWM
#define PIN_VALVE1      11    // valve MOSFET gates, active high
#define PIN_VALVE2      12
#define PIN_VALVE3      13
#define PIN_VALVE4      14
#define PIN_LED_WIFI    15    // status LED, active high
#define PIN_SENS_PWR_N  16    // sensor rail P-FET gate: LOW = sensors powered
#define PIN_SDA         17    // I2C header (spare)
#define PIN_SCL         18

#define NUM_ZONES 4

// ---- Analog scaling -----------------------------------------------------------
#define VIN_DIV_RATIO    ((100.0f + 22.0f) / 22.0f)   // 100 k over 22 k
#define ISENSE_V_PER_A   1.0f                         // 20 mOhm shunt x INA181A2 gain of 50
#define ISENSE_SAMPLES   16                           // ADC samples averaged per current reading
#define ISENSE_SAMPLE_US 31                           // 16 x 31 us = 0.5 ms = 10 PWM periods

// ---- Pump drive ---------------------------------------------------------------
#define PUMP_PWM_HZ      20000   // above the audible range
#define PUMP_PWM_BITS    10
#define SOFTSTART_MS     500     // length of the start-up ramp
#define SOFTSTART_STEPS  50      // one step every 10 ms
#define SOFTSTART_CHECK_FROM_DUTY 0.2f   // below this the duty-corrected reading is too noisy to use

// ---- Protection limits --------------------------------------------------------
#define MAX_ZONES_OPEN      2        // keeps the total inside a 12 V 3 A adapter
#define PUMP_MAX_CURRENT_A  2.5f     // overcurrent trip (stalled or shorted pump)
#define PUMP_DRY_CURRENT_A  0.25f    // below this while running means no water
#define DRY_RUN_GRACE_MS    5000UL   // ignore low current while the pump primes
#define VIN_MIN_V           10.5f
#define VIN_MAX_V           13.8f
#define VIN_FAULT_TICKS      2        // supply must be out of range on 2 safety ticks in a row (rejects short dips)
#define MAX_WATER_MS        (20UL * 60UL * 1000UL)   // hard cap per zone: 20 minutes
#define VALVE_LEAD_MS       100      // valve opens this long before the pump starts
#define PUMP_LAG_MS         50       // pump stops this long before the last valve closes

// ---- Watering thresholds (changeable from Blynk) ------------------------------
#define DEFAULT_DRY_PCT     35       // start watering below this
#define DEFAULT_WET_PCT     60       // stop watering at or above this
#define MIN_HYSTERESIS_PCT  5        // wet must stay at least this far above dry
#define SENSOR_PERIOD_MS    10000UL  // soil is read every 10 s

// ---- Moisture sensor calibration (12-bit raw ADC) ------------------------------
#define MOIST_RAW_DRY       3000     // reading in dry air
#define MOIST_RAW_WET       1200     // reading in water
#define MOIST_RAW_MIN       100      // below this the sensor is shorted or unplugged
#define MOIST_RAW_MAX       4000     // above this the sensor is open circuit
#define MOIST_SAMPLES       8
#define SENSOR_SETTLE_MS    150      // wait after powering the sensor rail

// ---- Task periods ---------------------------------------------------------------
#define SAFETY_PERIOD_MS    100UL
#define BUTTON_PERIOD_MS    20UL
#define STATUS_PERIOD_MS    1000UL

// ---- Wi-Fi and Blynk credentials -------------------------------------------------
// Copy secrets.example.h to secrets.h and fill it in. secrets.h is git-ignored.
#include "secrets.h"
